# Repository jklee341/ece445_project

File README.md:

# Rodent Deterrent and Classification System

Rodent deterrent and classification system

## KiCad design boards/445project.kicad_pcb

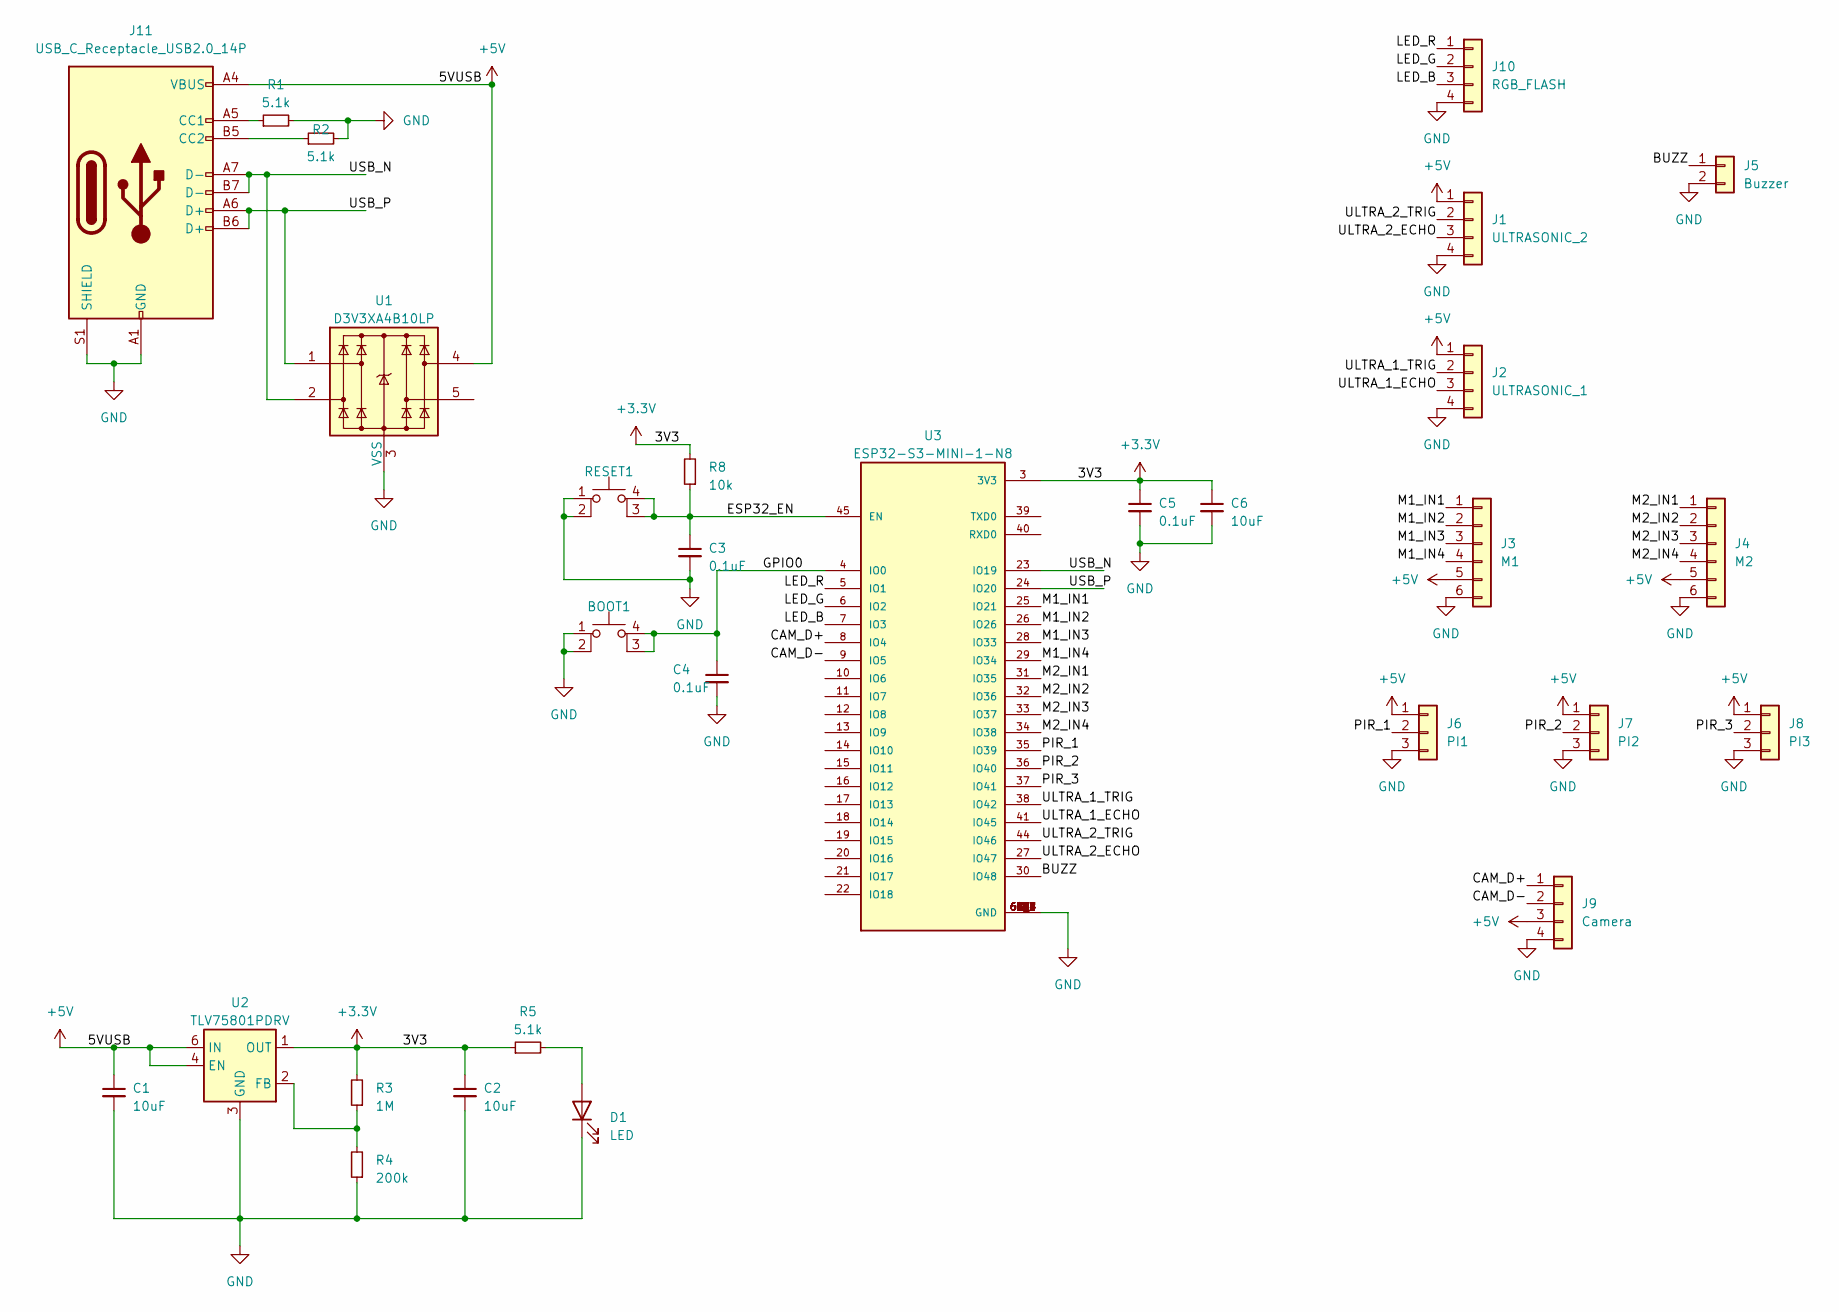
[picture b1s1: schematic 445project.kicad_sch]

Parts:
BOOT1: SW_SPST_PTS810
C1, C2, C6: 10uF; C_0603_1608Metric
C3, C4, C5: 0.1uF; C_0603_1608Metric
D1: LED; LED_0603_1608Metric
J1: ULTRASONIC_2; PinHeader_1x04_P2.54mm_Vertical
J2: ULTRASONIC_1; PinHeader_1x04_P2.54mm_Vertical
J3: M1; PinHeader_1x06_P2.54mm_Vertical
J4: M2; PinHeader_1x06_P2.54mm_Vertical
J5: Buzzer; PinHeader_1x02_P2.54mm_Vertical
J6: PI1; PinHeader_1x03_P2.54mm_Vertical
J7: PI2; PinHeader_1x03_P2.54mm_Vertical
J8: PI3; PinHeader_1x03_P2.54mm_Vertical
J9: Camera; PinHeader_1x04_P2.54mm_Vertical
J10: RGB_FLASH; PinHeader_1x04_P2.54mm_Vertical
J11: USB_C_Receptacle_USB2.0_14P; USB_C_Receptacle_GCT_USB4105-xx-A_16P_TopMnt_Horizontal
R1, R2, R5: 5.1k; R_0603_1608Metric
R3: 1M; R_0603_1608Metric
R4: 200k; R_0603_1608Metric
R8: 10k; R_0603_1608Metric
RESET1: SW_SPST_PTS810
U1: D3V3XA4B10LP; Diodes_UDFN-10_1.0x2.5mm_P0.5mm
U2: TLV75801PDRV; WSON-6-1EP_2x2mm_P0.65mm_EP1x1.6mm
U3: ESP32-S3-MINI-1-N8; XCVR_ESP32-S3-MINI-1-N8; PARTREV v0.6

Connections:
+3.3V: C2.1, C5.1, C6.1, R3.2, R5.1, R8.2, U2.1 (OUT), U3.3 (3V3)
+5V: C1.1, J1.1, J2.1, J3.5, J4.5, J6.1, J7.1, J8.1, J9.3, J11.A4 (VBUS), J11.A9 (VBUS), J11.B4 (VBUS), J11.B9 (VBUS), U1.4, U2.4 (EN), U2.6 (IN)
/BUZZ: J5.1, U3.30 (IO48)
/CAM_D+: J9.1, U3.8 (IO4)
/CAM_D-: J9.2, U3.9 (IO5)
/ESP32_EN: C3.1, R8.1, RESET1.3 (K), RESET1.4 (A), U3.45 (EN)
/GPIO0: BOOT1.3 (K), BOOT1.4 (A), C4.1, U3.4 (IO0)
/LED_B: J10.3, U3.7 (IO3)
/LED_G: J10.2, U3.6 (IO2)
/LED_R: J10.1, U3.5 (IO1)
/M1_IN1: J3.1, U3.25 (IO21)
/M1_IN2: J3.2, U3.26 (IO26)
/M1_IN3: J3.3, U3.28 (IO33)
/M1_IN4: J3.4, U3.29 (IO34)
/M2_IN1: J4.1, U3.31 (IO35)
/M2_IN2: J4.2, U3.32 (IO36)
/M2_IN3: J4.3, U3.33 (IO37)
/M2_IN4: J4.4, U3.34 (IO38)
/PIR_1: J6.2, U3.35 (IO39)
/PIR_2: J7.2, U3.36 (IO40)
/PIR_3: J8.2, U3.37 (IO41)
/ULTRA_1_ECHO: J2.3, U3.41 (IO45)
/ULTRA_1_TRIG: J2.2, U3.38 (IO42)
/ULTRA_2_ECHO: J1.3, U3.27 (IO47)
/ULTRA_2_TRIG: J1.2, U3.44 (IO46)
/USB_N: J11.A7 (D-), J11.B7 (D-), U1.2, U3.23 (IO19)
/USB_P: J11.A6 (D+), J11.B6 (D+), U1.1, U3.24 (IO20)
GND: BOOT1.1, BOOT1.2, C1.2, C2.2, C3.2, C4.2, C5.2, C6.2, D1.1 (K), J1.4, J2.4, J3.6, J4.6, J5.2, J6.3, J7.3, J8.3, J9.4, J10.4, J11.A1 (GND), J11.A12 (GND), J11.B1 (GND), J11.B12 (GND), J11.S1 (SHIELD), R1.2, R2.2, R4.1, RESET1.1, RESET1.2, U1.3 (VSS), U1.8 (VSS), U2.3 (GND), U2.7 (GND), U3.1 (GND), U3.2 (GND), U3.42 (GND), U3.43 (GND), U3.46 (GND), U3.47 (GND), U3.48 (GND), U3.49 (GND), U3.50 (GND), U3.51 (GND), U3.52 (GND), U3.53 (GND), U3.54 (GND), U3.55 (GND), U3.56 (GND), U3.57 (GND), U3.58 (GND), U3.59 (GND), U3.60 (GND), U3.61 (GND), U3.61_1 (GND), U3.61_2 (GND), U3.61_3 (GND), U3.61_4 (GND), U3.61_5 (GND), U3.61_6 (GND), U3.61_7 (GND), U3.61_8 (GND), U3.62 (GND), U3.63 (GND), U3.64 (GND), U3.65 (GND)
unnamed: D1.2 (A), R5.2
unnamed: J11.A5 (CC1), R1.1
unnamed: J11.B5 (CC2), R2.1
unnamed: R3.1, R4.2, U2.2 (FB)

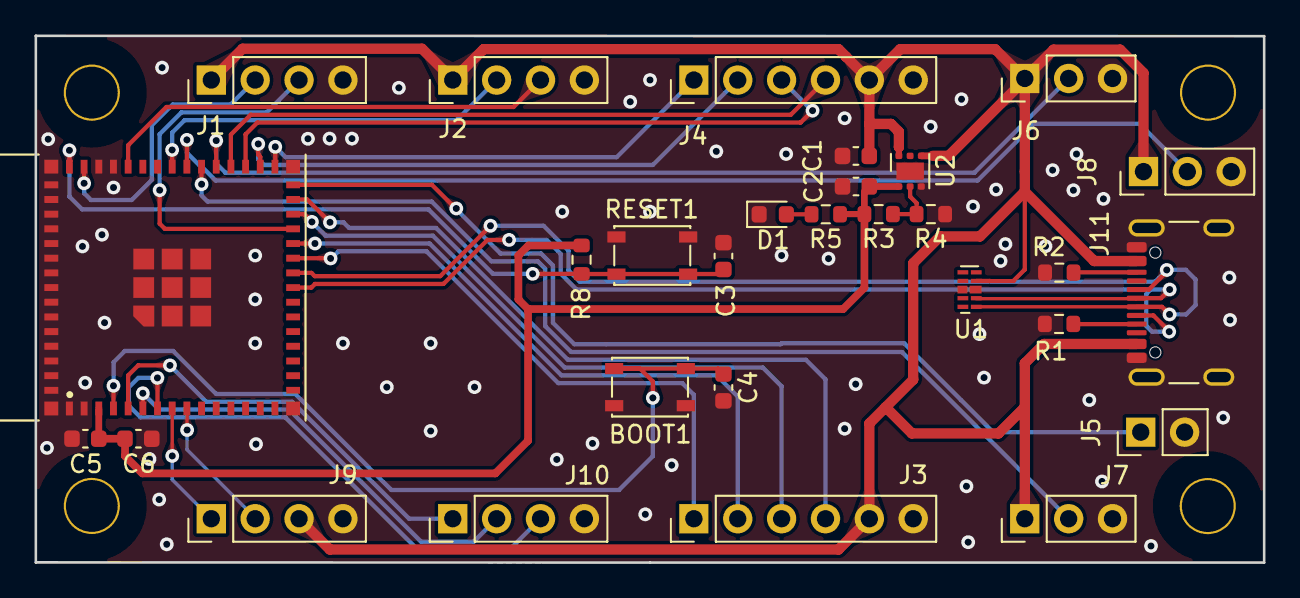
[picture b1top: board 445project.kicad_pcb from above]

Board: 2 copper layers, 71.1 x 30.5 mm, 29 parts (0 on the bottom side), 32 nets.

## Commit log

2024-02-06 adding subdirectories and blank files
2024-03-05 pcb schematic
2024-03-05 pcb version 1
2024-03-27 adding code to this repo
2024-04-01 finished initial detection for animal detection
2024-05-02 Update Readme.md
    forgot to updatre thisas i went through semester but this is my lab notebook over the sem
2024-06-26 add main1.py
2024-06-26 add detect.py
2024-06-26 add ultra_transducer_test.py
2024-06-26 add ultrasonicsensor.py
2024-06-26 add test_yolo.py
2024-06-26 add color.py
2024-06-26 add stream_test.py
2024-06-26 add servo.py
2024-06-26 add sensors.py
2024-06-26 add radar.py
2024-06-26 add pir_code.py
2024-06-26 add display.py
